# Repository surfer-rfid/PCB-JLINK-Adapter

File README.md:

# PCB-JLINK-Adapter
Kicad project for JLINK 9/10-pin to 4-pin adapter.

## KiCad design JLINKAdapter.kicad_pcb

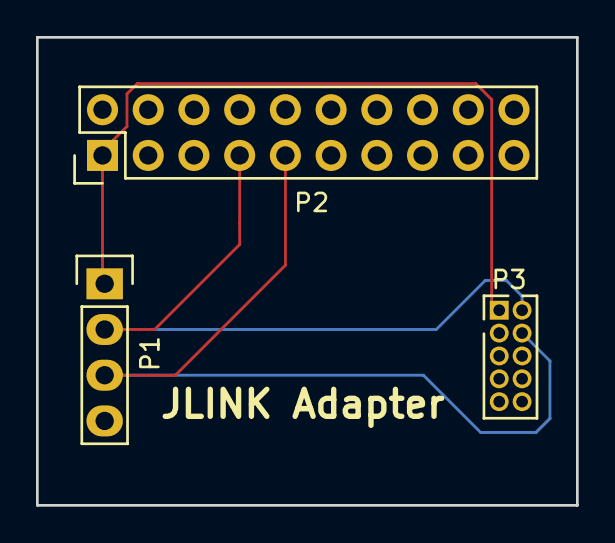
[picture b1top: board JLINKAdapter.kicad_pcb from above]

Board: 2 copper layers, 30.0 x 26.0 mm, 3 parts (0 on the bottom side), 4 nets.

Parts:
P1: CONN_01X04; Pin_Header_Straight_1x04
P2: CONN_02X10; Pin_Header_Straight_2x10
P3: CONN_02X05; Pin_Header_Straight_2x05_Pitch1.27mm

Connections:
/SWCLK: P1.3, P2.9, P3.4
/SWDIO: P1.2, P2.7, P3.2
/VTREF: P1.1, P2.1, P3.1
GND: P1.4, P2.4, P2.6, P2.8, P2.10, P2.12, P2.14, P2.16, P2.18, P2.20, P3.3, P3.5, P3.9

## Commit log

2021-01-30 Upload files from this repo.
    Upload files for the JLINK adapter for the first time.

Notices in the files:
JLINKAdapter.kicad_pcb:
Licensed under CERN-OHL-P v2 or later.
Copyright 2021 Superlative Semiconductor LLC.
